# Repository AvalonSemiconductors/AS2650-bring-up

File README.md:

# AS2650 bring-up
Hardware and Software used during bring-up of the GFMPW-0 AS2650.

## Repository Contents

`HW` - PCB design for the custom bring-up board with 8KiB of SRAM

`GAL` - AND term listing for the GAL device on the PCB - Can be assembled using [galette](https://github.com/simon-frankau/galette).

`Firmware` - Management Controller Firmware for the PCB - Must be used together with the headers and utils from [caravel_board](https://github.com/efabless/caravel_board/tree/main/firmware/gf180).

`Programs` - Programs written in AS2650 assembly - contains its own README.

`Bugs` - Contains a README documenting all silicon bugs, their severity, and possible workarounds.

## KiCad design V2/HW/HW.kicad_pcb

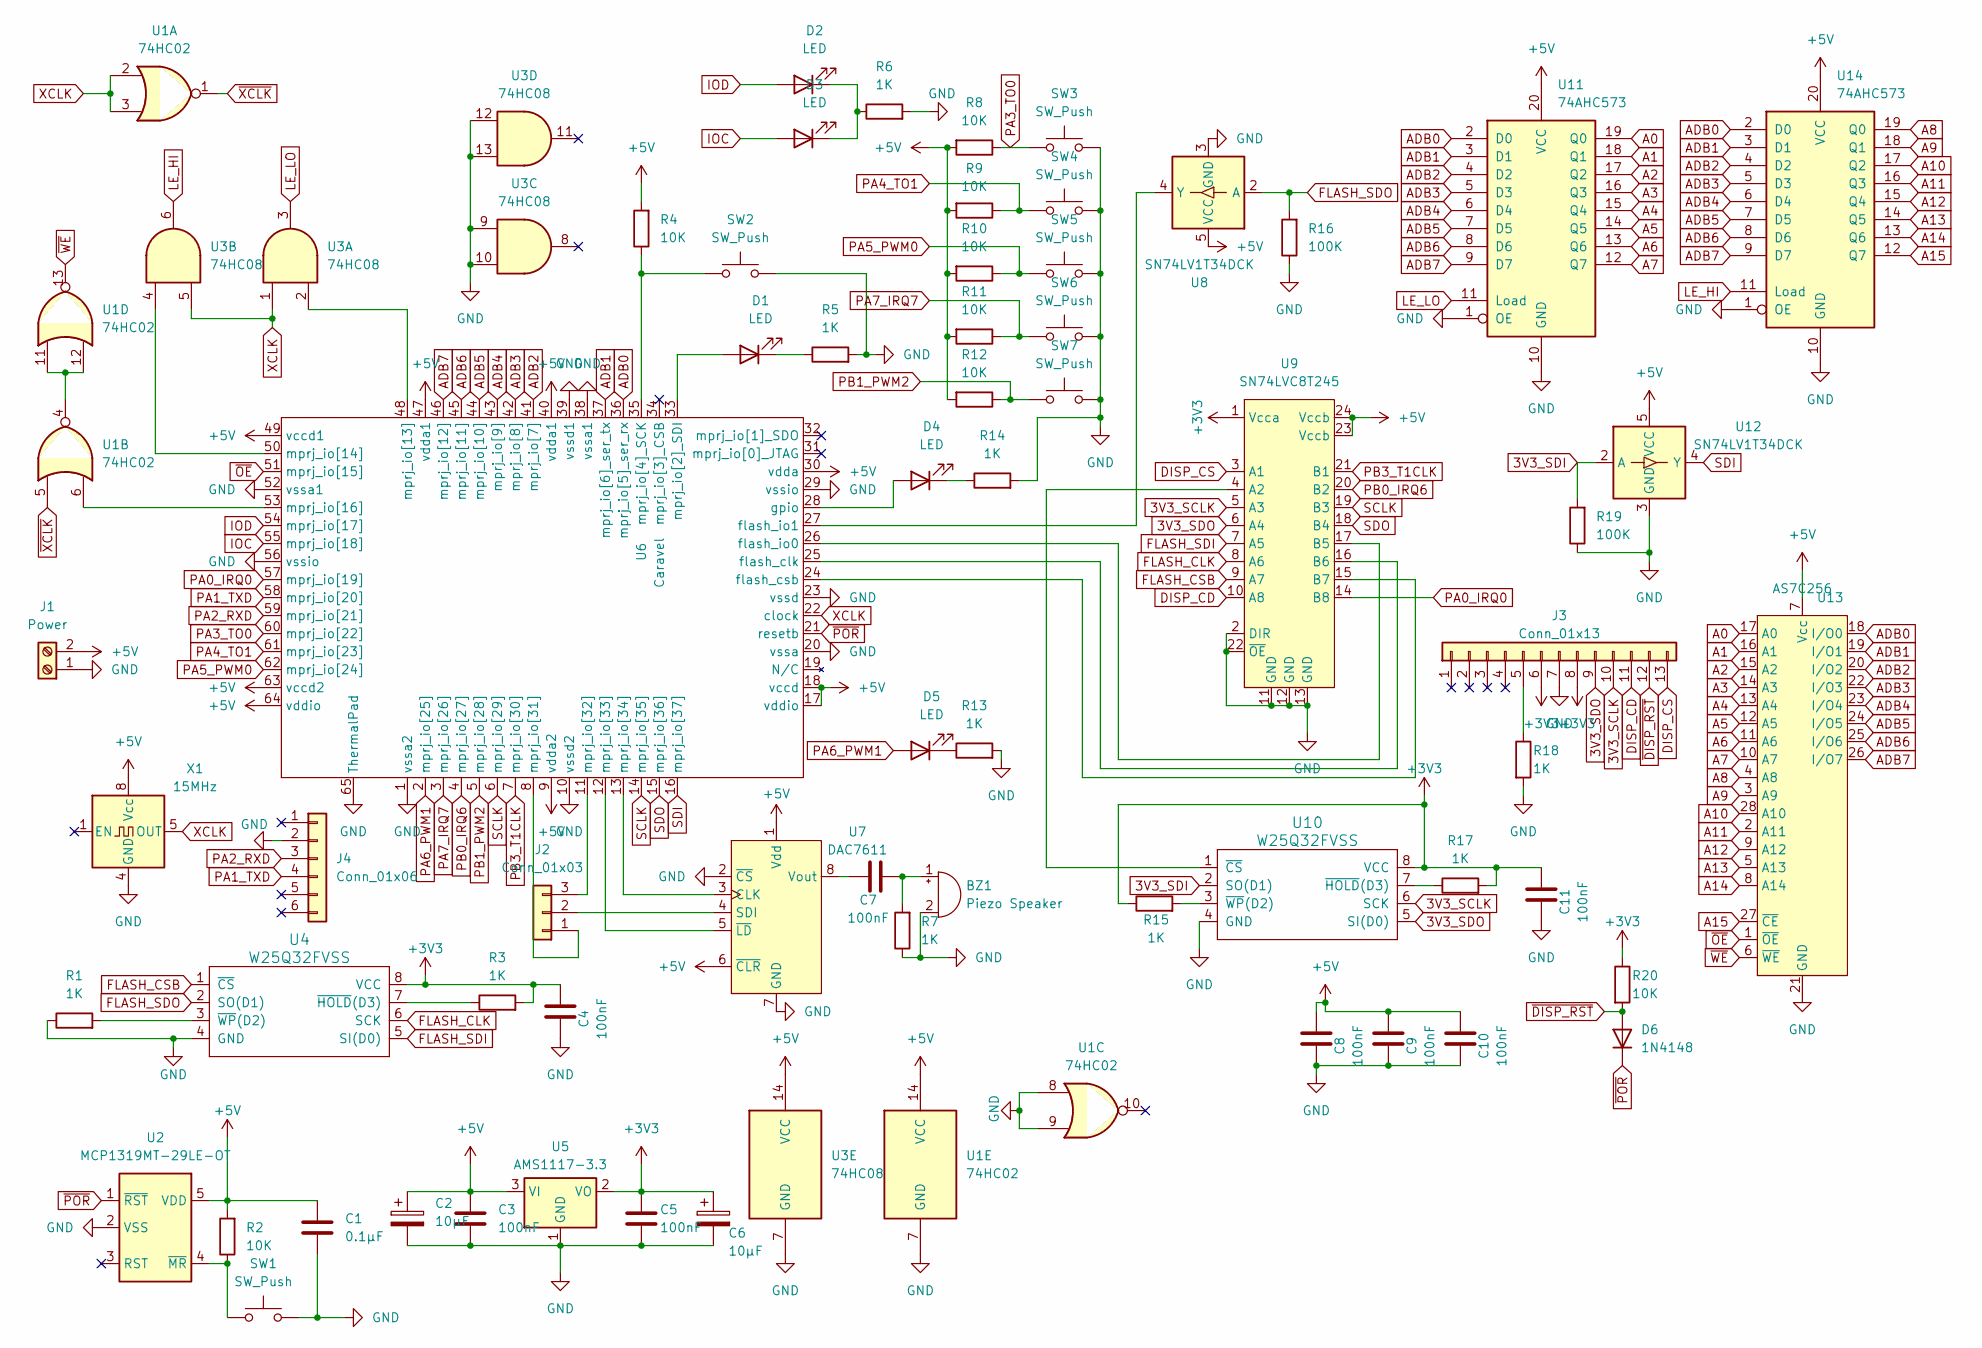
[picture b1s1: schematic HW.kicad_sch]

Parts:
BZ1: Piezo Speaker; Buzzer_12x9.5RM7.6
C1: 0.1µF; C_1206_3216Metric_Pad1.33x1.80mm_HandSolder
C2, C6: 10µF; CP_Radial_D4.0mm_P2.00mm
C3, C5: 100nF; C_1206_3216Metric_Pad1.33x1.80mm_HandSolder
C4, C7, C8, C9, C10, C11: 100nF; C_0805_2012Metric
D1, D2, D3, D4, D5: LED; LED_1206_3216Metric_Pad1.42x1.75mm_HandSolder
D6: 1N4148; D_DO-34_SOD68_P7.62mm_Horizontal
J1: Power; TerminalBlock_bornier-2_P5.08mm
J2: Conn_01x03; PinHeader_1x03_P2.54mm_Vertical
J3: Conn_01x13; PinHeader_1x13_P2.54mm_Vertical
J4: Conn_01x06; PinSocket_1x06_P2.54mm_Vertical
R1, R3, R5, R6, R7, R13, R14, R15, R17, R18: 1K; R_1206_3216Metric_Pad1.30x1.75mm_HandSolder
R2, R4, R8, R9, R10, R11, R12, R20: 10K; R_1206_3216Metric_Pad1.30x1.75mm_HandSolder
R16, R19: 100K; R_1206_3216Metric_Pad1.30x1.75mm_HandSolder
SW1, SW2, SW3, SW4, SW5, SW6, SW7: SW_Push; SW_PUSH_6mm
U1: 74HC02; SO-14_3.9x8.65mm_P1.27mm
U2: MCP1319MT-29LE-OT; SOT-23-5
U3: 74HC08; SO-14_3.9x8.65mm_P1.27mm
U4, U10: W25Q32FVSS; DIP-8_W7.62mm
U5: AMS1117-3.3; SOT-223-3_TabPin2
U6: Caravel; QFN-64-1EP_9x9mm_P0.5mm_EP7.65x7.65mm
U7: DAC7611; DIP-8_W7.62mm
U8, U12: SN74LV1T34DCK; SOT-23-5
U9: SN74LVC8T245; TSSOP-24_4.4x7.8mm_P0.65mm
U11, U14: 74AHC573; TSSOP-20_4.4x6.5mm_P0.65mm
U13: AS7C256; TSOP-I-28_11.8x8mm_P0.55mm
X1: 15MHz; Oscillator_DIP-8

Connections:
3V3_SCLK: J3.10, U9.5 (A3), U10.6 (SCK)
3V3_SDI: R19.2, U10.2 (SO(D1)), U12.2 (A)
3V3_SDO: J3.9, U9.6 (A4), U10.5 (SI(D0))
+3V3: C4.2, C5.1, C6.1, C11.2, J3.6, J3.8, R3.2, R15.1, R17.2, R20.1, U4.8 (VCC), U5.2 (VO), U9.1 (Vcca), U10.8 (VCC)
+5V: C1.2, C2.1, C3.1, C8.2, C9.2, C10.2, J1.2, R2.2, R4.2, R8.2, R9.2, R10.2, R11.2, R12.2, U1.14 (VCC), U2.5 (VDD), U3.14 (VCC), U5.3 (VI), U6.9 (vdda2), U6.17 (vddio), U6.18 (vccd), U6.30 (vdda), U6.40 (vdda1), U6.47 (vdda1), U6.49 (vccd1), U6.63 (vccd2), U6.64 (vddio), U7.1 (Vdd), U7.6 (~CLR), U8.5 (VCC), U9.23 (Vccb), U9.24 (Vccb), U11.20 (VCC), U12.5 (VCC), U13.7 (Vcc), U14.20 (VCC), X1.8 (Vcc)
A0: U11.19 (Q0), U13.17 (A0)
A1: U11.18 (Q1), U13.16 (A1)
A2: U11.17 (Q2), U13.15 (A2)
A3: U11.16 (Q3), U13.14 (A3)
A4: U11.15 (Q4), U13.13 (A4)
A5: U11.14 (Q5), U13.12 (A5)
A6: U11.13 (Q6), U13.11 (A6)
A7: U11.12 (Q7), U13.10 (A7)
A8: U13.4 (A8), U14.19 (Q0)
A9: U13.3 (A9), U14.18 (Q1)
A10: U13.28 (A10), U14.17 (Q2)
A11: U13.2 (A11), U14.16 (Q3)
A12: U13.9 (A12), U14.15 (Q4)
A13: U13.5 (A13), U14.14 (Q5)
A14: U13.8 (A14), U14.13 (Q6)
A15: U13.27 (~CE), U14.12 (Q7)
ADB0: U6.36 (mprj_io[5]_ser_rx), U11.2 (D0), U13.18 (I/O0), U14.2 (D0)
ADB1: U6.37 (mprj_io[6]_ser_tx), U11.3 (D1), U13.19 (I/O1), U14.3 (D1)
ADB2: U6.41 (mprj_io[7]), U11.4 (D2), U13.20 (I/O2), U14.4 (D2)
ADB3: U6.42 (mprj_io[8]), U11.5 (D3), U13.22 (I/O3), U14.5 (D3)
ADB4: U6.43 (mprj_io[9]), U11.6 (D4), U13.23 (I/O4), U14.6 (D4)
ADB5: U6.44 (mprj_io[10]), U11.7 (D5), U13.24 (I/O5), U14.7 (D5)
ADB6: U6.45 (mprj_io[11]), U11.8 (D6), U13.25 (I/O6), U14.8 (D6)
ADB7: U6.46 (mprj_io[12]), U11.9 (D7), U13.26 (I/O7), U14.9 (D7)
DISP_CD: J3.11, U9.10 (A8)
DISP_CS: J3.13, U9.3 (A1)
FLASH_CLK: U4.6 (SCK), U9.8 (A6)
FLASH_CSB: U4.1 (~CS), U9.9 (A7)
FLASH_SDI: U4.5 (SI(D0)), U9.7 (A5)
FLASH_SDO: R16.2, U4.2 (SO(D1)), U8.2 (A)
GND: BZ1.2 (+), C1.1, C2.2, C3.2, C4.1, C5.2, C6.2, C8.1, C9.1, C10.1, C11.1, J1.1, J3.7, J4.2, R1.1, R5.2, R6.2, R7.1, R13.2, R14.2, R16.1, R18.2, R19.1, SW1.2, SW2.2, SW3.2, SW4.2, SW5.2, SW6.2, SW7.2, U1.7 (GND), U1.8, U1.9, U2.2 (VSS), U3.7 (GND), U3.9, U3.10, U3.12, U3.13, U4.4 (GND), U5.1 (GND), U6.1 (vssa2), U6.10 (vssd2), U6.20 (vssa), U6.23 (vssd), U6.29 (vssio), U6.38 (vssa1), U6.39 (vssd1), U6.52 (vssa1), U6.56 (vssio), U6.65 (ThermalPad), U7.2 (~CS), U7.7 (GND), U8.3 (GND), U9.2 (DIR), U9.11 (GND), U9.12 (GND), U9.13 (GND), U9.22 (~OE), U10.4 (GND), U11.1 (OE), U11.10 (GND), U12.3 (GND), U13.21 (GND), U14.1 (OE), U14.10 (GND), X1.4 (GND)
IOC: D3.2 (A), U6.55 (mprj_io[18])
IOD: D2.2 (A), U6.54 (mprj_io[17])
LE_HI: U3.6, U14.11 (Load)
LE_LO: U3.3, U11.11 (Load)
unnamed: BZ1.1 (-), C7.2, R7.2
unnamed: D1.2 (A), U6.33 (mprj_io[2]_SDI)
unnamed: D1.1 (K), R5.1
unnamed: D2.1 (K), D3.1 (K), R6.1
unnamed: D4.2 (A), U6.28 (gpio)
unnamed: D4.1 (K), R14.1
unnamed: D5.1 (K), R13.1
unnamed: J2.1, U6.8 (mprj_io[31])
unnamed: J2.2, U7.4 (SDI)
unnamed: J2.3, U6.11 (mprj_io[32])
unnamed: J3.5, R18.1
unnamed: U1.4, U1.11, U1.12
unnamed: R2.1, SW1.1, U2.4 (~MR)
unnamed: R3.1, U4.7 (~HOLD(D3))
unnamed: R1.2, U4.3 (~WP(D2))
unnamed: U6.25 (flash_clk), U9.16 (B6)
unnamed: U6.24 (flash_csb), U9.15 (B7)
unnamed: U6.26 (flash_io0), U9.17 (B5)
unnamed: U6.27 (flash_io1), U8.4 (Y)
unnamed: R4.1, SW2.1, U6.35 (mprj_io[4]_SCK)
unnamed: U3.2, U6.48 (mprj_io[13])
unnamed: U3.4, U6.50 (mprj_io[14])
unnamed: U1.6, U6.53 (mprj_io[16])
unnamed: U6.12 (mprj_io[33]), U7.5 (~LD)
unnamed: U6.13 (mprj_io[34]), U7.3 (CLK)
unnamed: C7.1, U7.8 (Vout)
unnamed: U9.4 (A2), U10.1 (~CS)
unnamed: R17.1, U10.7 (~HOLD(D3))
unnamed: R15.2, U10.3 (~WP(D2))
PA0_IRQ0: U6.57 (mprj_io[19]), U9.14 (B8)
PA1_TXD: J4.4, U6.58 (mprj_io[20])
PA2_RXD: J4.3, U6.59 (mprj_io[21])
PA3_TO0: R8.1, SW3.1, U6.60 (mprj_io[22])
PA4_TO1: R9.1, SW4.1, U6.61 (mprj_io[23])
PA5_PWM0: R10.1, SW5.1, U6.62 (mprj_io[24])
PA6_PWM1: D5.2 (A), U6.2 (mprj_io[25])
PA7_IRQ7: R11.1, SW6.1, U6.3 (mprj_io[26])
PB0_IRQ6: U6.4 (mprj_io[27]), U9.20 (B2)
PB1_PWM2: R12.1, SW7.1, U6.5 (mprj_io[28])
PB3_T1CLK: U6.7 (mprj_io[30]), U9.21 (B1)
SCLK: U6.6 (mprj_io[29]), U6.14 (mprj_io[35]), U9.19 (B3)
SDI: U6.16 (mprj_io[37]), U12.4 (Y)
SDO: U6.15 (mprj_io[36]), U9.18 (B4)
XCLK: U1.2, U1.3, U3.1, U3.5, U6.22 (clock), X1.5 (OUT)
~DISP_RST: D6.2 (A), J3.12, R20.2
~OE: U6.51 (mprj_io[15]), U13.1 (~OE)
~POR: D6.1 (K), U2.1 (~RST), U6.21 (resetb)
~WE: U1.13, U13.6 (~WE)
~XCLK: U1.1, U1.5

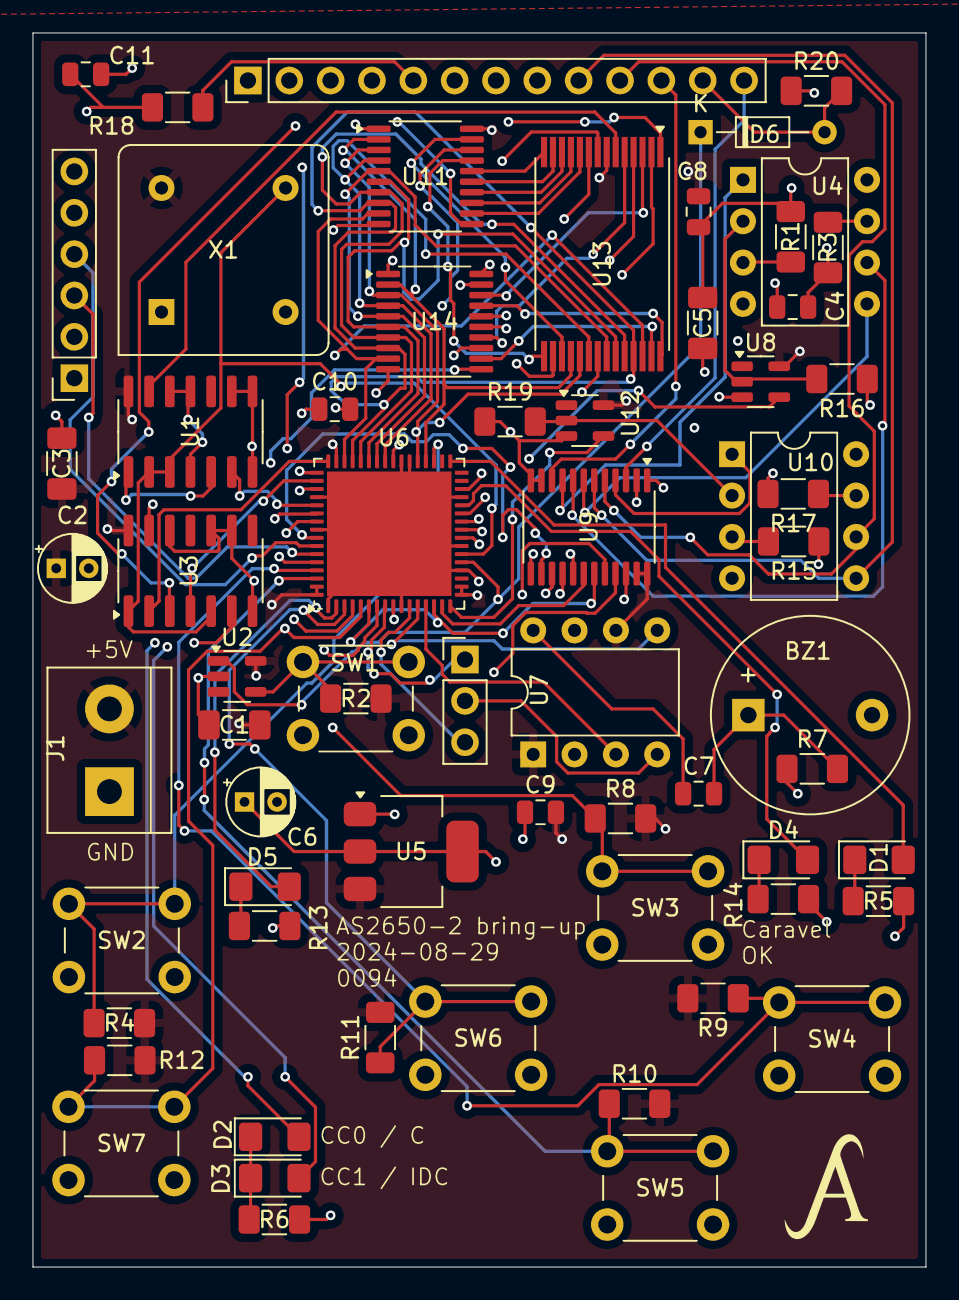
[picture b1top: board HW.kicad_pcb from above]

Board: 4 copper layers, 54.9 x 75.8 mm, 64 parts (0 on the bottom side), 89 nets.

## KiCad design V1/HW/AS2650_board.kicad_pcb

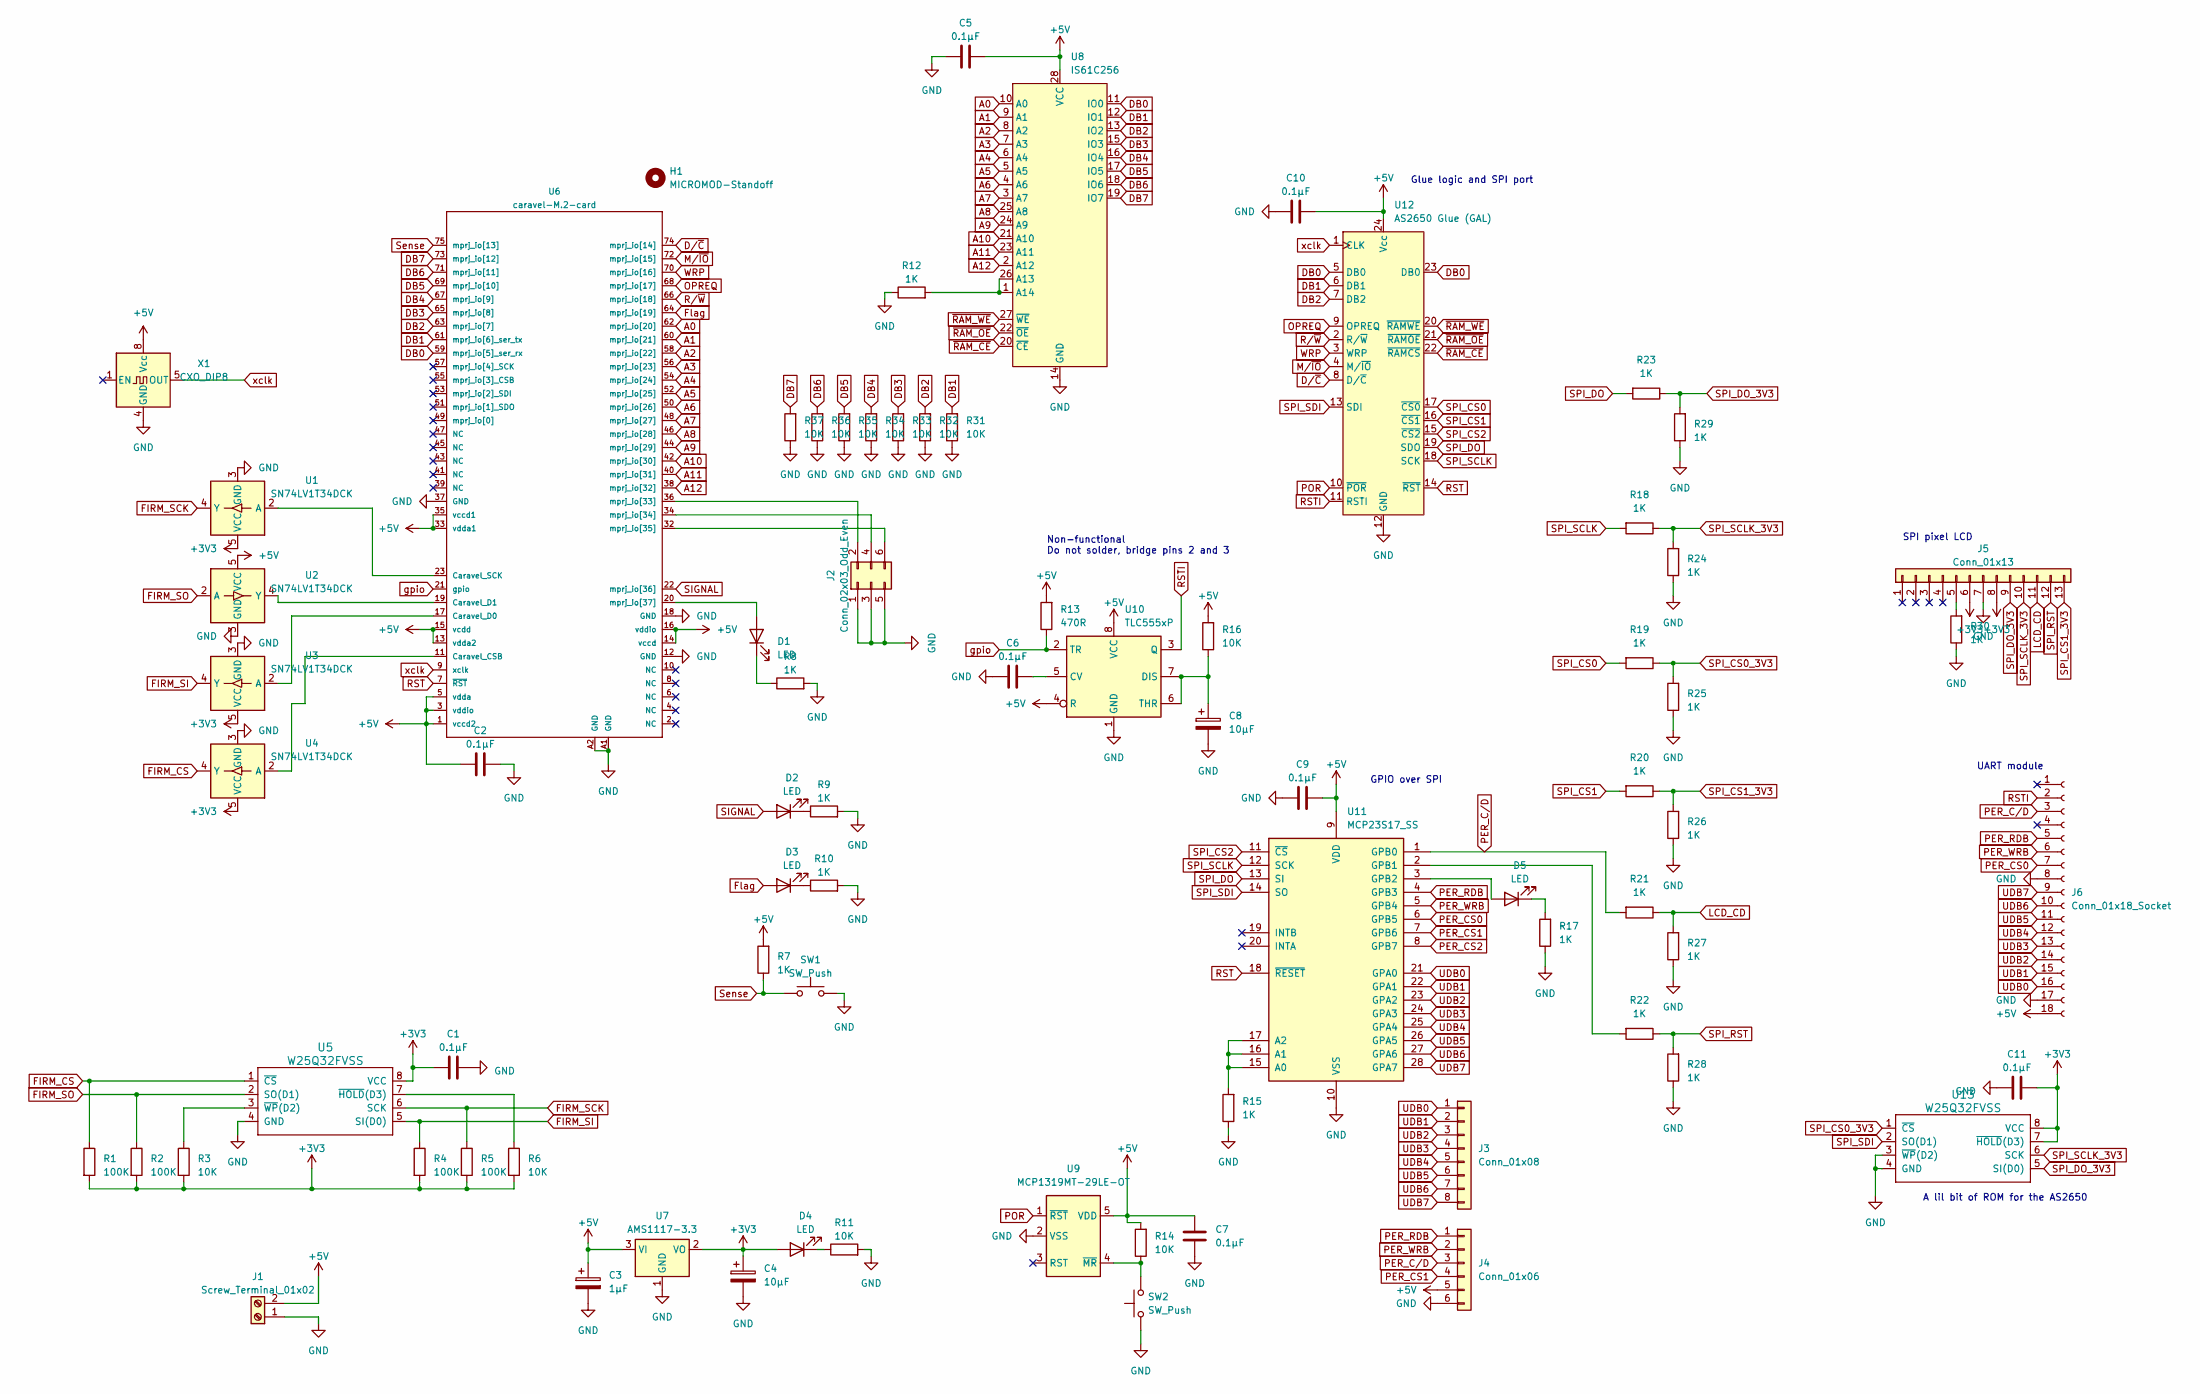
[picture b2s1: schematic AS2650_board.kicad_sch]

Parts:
C1, C2, C5, C6, C7, C9, C10, C11: 0.1µF; C_1206_3216Metric_Pad1.33x1.80mm_HandSolder
C3: 1µF; CP_Radial_D4.0mm_P2.00mm
C4, C8: 10µF; CP_Radial_D4.0mm_P2.00mm
D1, D2, D3, D4, D5: LED; LED_2010_5025Metric_Pad1.52x2.65mm_HandSolder
H1: MICROMOD-Standoff; MicroMod-Standoff
J1: Screw_Terminal_01x02; TerminalBlock_bornier-2_P5.08mm
J2: Conn_02x03_Odd_Even; PinHeader_2x03_P2.54mm_Vertical
J3: Conn_01x08; PinSocket_1x08_P2.54mm_Vertical
J4: Conn_01x06; PinSocket_1x06_P2.54mm_Vertical
J5: Conn_01x13; PinSocket_1x13_P2.54mm_Vertical
J6: Conn_01x18_Socket; PinSocket_1x18_P2.54mm_Vertical
R1, R2, R4, R5: 100K; R_1206_3216Metric_Pad1.30x1.75mm_HandSolder
R3, R6, R11, R14, R16, R31, R32, R33, R34, R35, R36, R37: 10K; R_1206_3216Metric_Pad1.30x1.75mm_HandSolder
R7, R8, R9, R10, R12, R15, R17, R18, R19, R20, R21, R22, R23, R24, R25, R26, R27, R28, R29, R30: 1K; R_1206_3216Metric_Pad1.30x1.75mm_HandSolder
R13: 470R; R_2010_5025Metric_Pad1.40x2.65mm_HandSolder
SW1, SW2: SW_Push; SW_PUSH_6mm
U1, U2, U3, U4: SN74LV1T34DCK; SOT-353_SC-70-5
U5, U13: W25Q32FVSS; DIP-8_W7.62mm
U6: caravel-M.2-card; M.2-CONNECTOR-E
U7: AMS1117-3.3; SOT-223-3_TabPin2
U8: IS61C256; DIP-28_W7.62mm
U9: MCP1319MT-29LE-OT; PoR_5_SOT23
U10: TLC555xP; DIP-8_W7.62mm
U11: MCP23S17_SS; SSOP-28_5.3x10.2mm_P0.65mm
U12: AS2650 Glue (GAL); DIP-24_W7.62mm
X1: CXO_DIP8; Oscillator_DIP-8

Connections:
+3V3: C1.1, C4.1, C11.2, D4.2 (A), J5.6, J5.8, R1.2, R2.2, R3.2, R4.2, R5.2, R6.2, U1.5 (VCC), U3.5 (VCC), U4.5 (VCC), U5.8 (VCC), U7.2 (VO), U13.7 (~HOLD(D3)), U13.8 (VCC)
+5V: C2.1, C3.1, C5.2, C7.2, C9.2, C10.2, J1.2, J4.5, J6.18, R7.2, R13.2, R14.2, R16.2, U2.5 (VCC), U6.1 (vccd2), U6.3 (vddio), U6.5 (vdda), U6.13 (vdda2), U6.14 (vccd), U6.15 (vcdd), U6.16 (vddio), U6.33 (vdda1), U6.35 (vccd1), U7.3 (VI), U8.28 (VCC), U9.5 (VDD), U10.4 (R), U10.8 (VCC), U11.9 (VDD), U12.24 (VCC), X1.8 (Vcc)
A0: U6.62 (mprj_io[20]), U8.10 (A0)
A1: U6.60 (mprj_io[21]), U8.9 (A1)
A2: U6.58 (mprj_io[22]), U8.8 (A2)
A3: U6.56 (mprj_io[23]), U8.7 (A3)
A4: U6.54 (mprj_io[24]), U8.6 (A4)
A5: U6.52 (mprj_io[25]), U8.5 (A5)
A6: U6.50 (mprj_io[26]), U8.4 (A6)
A7: U6.48 (mprj_io[27]), U8.3 (A7)
A8: U6.46 (mprj_io[28]), U8.25 (A8)
A9: U6.44 (mprj_io[29]), U8.24 (A9)
A10: U6.42 (mprj_io[30]), U8.21 (A10)
A11: U6.40 (mprj_io[31]), U8.23 (A11)
A12: U6.38 (mprj_io[32]), U8.2 (A12)
DB0: U6.59 (mprj_io[5]_ser_rx), U8.11 (IO0), U12.5 (I), U12.23 (I/O)
DB1: R31.2, U6.61 (mprj_io[6]_ser_tx), U8.12 (IO1), U12.6 (I)
DB2: R32.2, U6.63 (mprj_io[7]), U8.13 (IO2), U12.7 (I)
DB3: R33.2, U6.65 (mprj_io[8]), U8.15 (IO3)
DB4: R34.2, U6.67 (mprj_io[9]), U8.16 (IO4)
DB5: R35.2, U6.69 (mprj_io[10]), U8.17 (IO5)
DB6: R36.2, U6.71 (mprj_io[11]), U8.18 (IO6)
DB7: R37.2, U6.73 (mprj_io[12]), U8.19 (IO7)
D/~C: U6.74 (mprj_io[14]), U12.8 (I)
FIRM_CS: R1.1, U4.4 (Y), U5.1 (~CS)
FIRM_SCK: R5.1, U1.4 (Y), U5.6 (SCK)
FIRM_SI: R4.1, U3.4 (Y), U5.5 (SI(D0))
FIRM_SO: R2.1, U2.2 (A), U5.2 (SO(D1))
Flag: D3.2 (A), U6.64 (mprj_io[19])
GND: C1.2, C2.2, C3.2, C4.2, C5.1, C6.1, C7.1, C8.2, C9.1, C10.1, C11.1, J1.1, J2.1, J2.3, J2.5, J4.6, J5.7, J6.8, J6.17, R8.2, R9.2, R10.2, R11.2, R12.1, R15.1, R17.1, R24.1, R25.1, R26.1, R27.1, R28.1, R29.1, R30.1, R31.1, R32.1, R33.1, R34.1, R35.1, R36.1, R37.1, SW1.2, SW2.1, U1.3 (GND), U2.3 (GND), U3.3 (GND), U4.3 (GND), U5.4 (GND), U6.12 (GND), U6.18 (GND), U6.37 (GND), U6.A1 (GND), U6.A2 (GND), U7.1 (GND), U8.14 (GND), U9.2 (VSS), U10.1 (GND), U11.10 (VSS), U12.12 (GND), U13.3 (~WP(D2)), U13.4 (GND), X1.4 (GND)
LCD_CD: J5.11, R21.1, R27.2
M/~IO: U6.72 (mprj_io[15]), U12.4 (I)
unnamed: D1.2 (A), U6.20 (mprj_io[37])
unnamed: D1.1 (K), R8.1
unnamed: D2.1 (K), R9.1
unnamed: D3.1 (K), R10.1
unnamed: D4.1 (K), R11.1
unnamed: D5.2 (A), U11.3 (GPB2)
unnamed: D5.1 (K), R17.2
unnamed: J2.2, U6.36 (mprj_io[33])
unnamed: J2.4, U6.34 (mprj_io[34])
unnamed: J2.6, U6.32 (mprj_io[35])
unnamed: J5.5, R30.2
unnamed: U1.2 (A), U6.23 (Caravel_SCK)
unnamed: U2.4 (Y), U6.19 (Caravel_D1)
unnamed: U3.2 (A), U6.17 (Caravel_D0)
unnamed: U4.2 (A), U6.11 (Caravel_CSB)
unnamed: R6.1, U5.7 (~HOLD(D3))
unnamed: R3.1, U5.3 (~WP(D2))
unnamed: R12.2, U8.1 (A14), U8.26 (A13)
unnamed: R14.1, SW2.2, U9.4 (~MR)
unnamed: C6.2, U10.5 (CV)
unnamed: C8.1, R16.1, U10.6 (THR), U10.7 (DIS)
unnamed: R15.2, U11.15 (A0), U11.16 (A1), U11.17 (A2)
unnamed: R22.2, U11.2 (GPB1)
OPREQ: U6.68 (mprj_io[17]), U12.9 (I)
PER_CS0: J6.7, U11.6 (GPB5)
PER_CS1: J4.4, U11.7 (GPB6)
PER_CS2: U11.8 (GPB7)
PER_C/D: J4.3, J6.3, R21.2, U11.1 (GPB0)
PER_RDB: J4.1, J6.5, U11.4 (GPB3)
PER_WRB: J4.2, J6.6, U11.5 (GPB4)
POR: U9.1 (~RST), U12.10 (I)
RST: U6.7 (~RST), U11.18 (~RESET), U12.14 (I/O)
RSTI: J6.2, U10.3 (Q), U12.11 (I)
R/~W: U6.66 (mprj_io[18]), U12.2 (I)
SIGNAL: D2.2 (A), U6.22 (mprj_io[36])
SPI_CS0: R19.2, U12.17 (I/O)
SPI_CS0_3V3: R19.1, R25.2, U13.1 (~CS)
SPI_CS1: R20.2, U12.16 (I/O)
SPI_CS1_3V3: J5.13, R20.1, R26.2
SPI_CS2: U11.11 (~CS), U12.15 (I/O)
SPI_DO: R23.2, U11.13 (SI), U12.19 (I/O)
SPI_DO_3V3: J5.9, R23.1, R29.2, U13.5 (SI(D0))
SPI_RST: J5.12, R22.1, R28.2
SPI_SCLK: R18.2, U11.12 (SCK), U12.18 (I/O)
SPI_SCLK_3V3: J5.10, R18.1, R24.2, U13.6 (SCK)
SPI_SDI: U11.14 (SO), U12.13 (I/O), U13.2 (SO(D1))
Sense: R7.1, SW1.1, U6.75 (mprj_io[13])
UDB0: J3.1, J6.16, U11.21 (GPA0)
UDB1: J3.2, J6.15, U11.22 (GPA1)
UDB2: J3.3, J6.14, U11.23 (GPA2)
UDB3: J3.4, J6.13, U11.24 (GPA3)
UDB4: J3.5, J6.12, U11.25 (GPA4)
UDB5: J3.6, J6.11, U11.26 (GPA5)
UDB6: J3.7, J6.10, U11.27 (GPA6)
UDB7: J3.8, J6.9, U11.28 (GPA7)
WRP: U6.70 (mprj_io[16]), U12.3 (I)
gpio: R13.1, U6.21 (gpio), U10.2 (TR)
xclk: U6.9 (xclk), U12.1 (I), X1.5 (OUT)
~RAM_CE: U8.20 (~CE), U12.22 (I/O)
~RAM_OE: U8.22 (~OE), U12.21 (I/O)
~RAM_WE: U8.27 (~WE), U12.20 (I/O)

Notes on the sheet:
Glue logic and SPI port
GPIO over SPI
Non-functional Do not solder, bridge pins 2 and 3
SPI pixel LCD
UART module
A lil bit of ROM for the AS2650

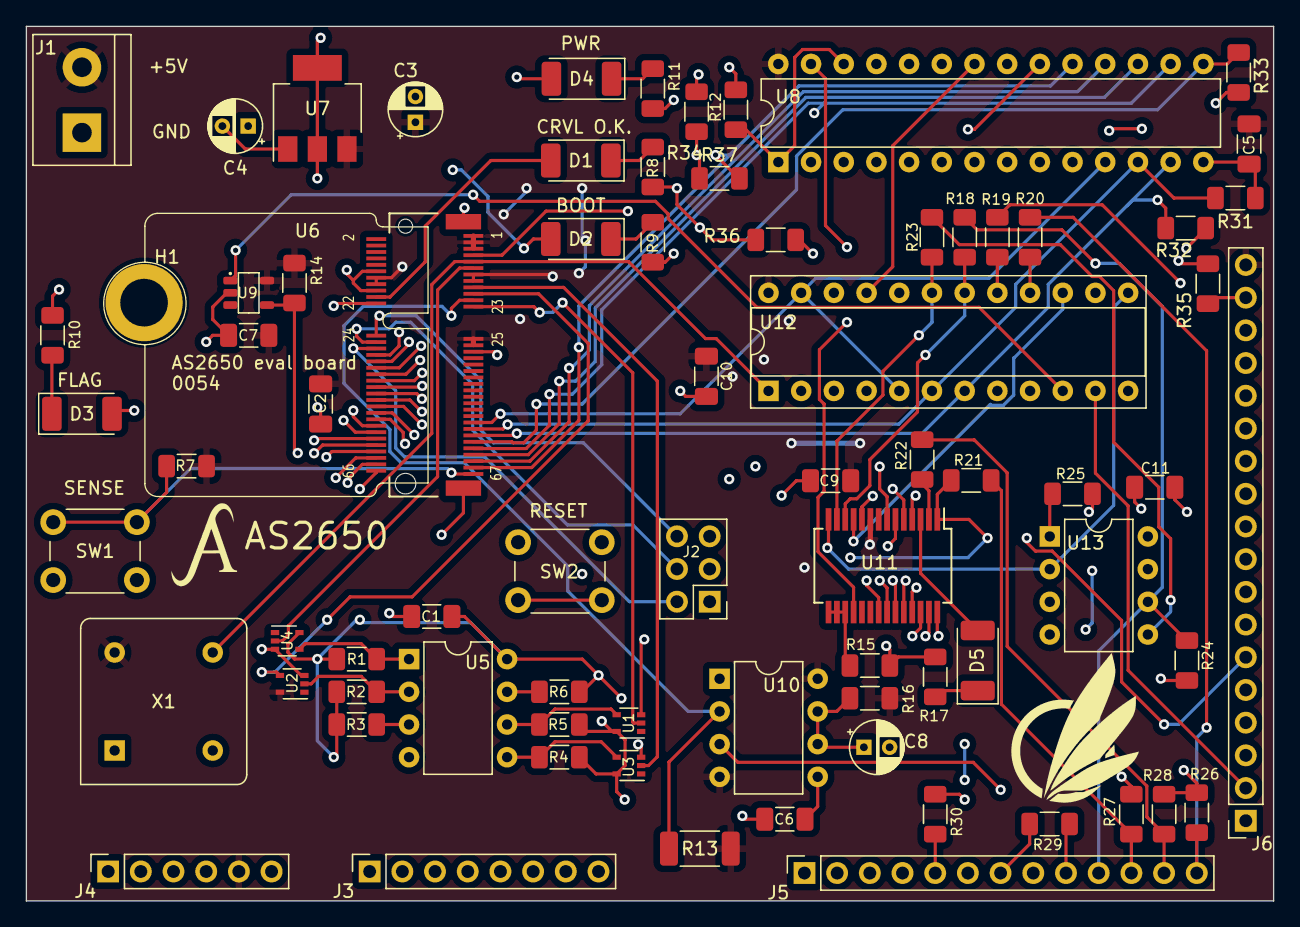
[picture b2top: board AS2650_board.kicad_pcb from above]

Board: 4 copper layers, 96.9 x 67.9 mm, 76 parts (0 on the bottom side), 92 nets.

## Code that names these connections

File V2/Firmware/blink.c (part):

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
void configure_io(uint8_t sel, uint8_t uart_en) {

//  ======= Useful GPIO mode values =============

//      GPIO_MODE_MGMT_STD_INPUT_NOPULL
//      GPIO_MODE_MGMT_STD_INPUT_PULLDOWN
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}

#undef INTERNAL_RAM
//#define debug_reg_base 0b000010000 //Normal IOD/IOC pins
//#define debug_reg_base 0b000010010 //Debug Carries
#define debug_reg_base 0b000010001 //Debug Condition Code

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
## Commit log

2023-07-06 PCB Hardware
2023-07-06 Firmware and Software.
2023-07-06 Bug listing
2023-07-07 Fix hold time violations on SRAM.
2023-07-14 Update mandel.asm to use hardware multiply
2023-07-14 Update emiss.asm with hardware muls
2024-04-21 More bug workarounds and proper reset functionality in firmware.
2024-08-19 Re-structure repo for V2 bring-up.
2024-09-24 V2 bring-up complete
2025-01-02 VFD Test Program
2025-06-18 Minimal Setup Example
2025-06-19 Add missing utils
2025-06-19 MinimalExample fixes
2025-09-22 Video signal generator test program
2025-09-28 Make video.asm use a higher input clock
2025-09-28 Fix shape in video.asm

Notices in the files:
V2/HW/HW.kicad_pcb:
CC0 / C
